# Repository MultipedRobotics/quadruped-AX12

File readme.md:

# AX-12A Quadruped

Features:

- Robotis AX-12A servos
- 4 legs
    - 4 servos per leg for added degrees of freedom
- Raspberry Pi 3 controlled w/camera
- Robotis lidar for obstacle avoidance and SLAM
- 12V power system
- Externally powered so no limit on run time
    - A battery could be designed and integrated

# Hardware

**Still under development**

- [Mechanical Hardware](mechanical/)
- [Electrical Hardware](electrical/)

# Software

Uses [multiped library](https://github.com/MultipedRobotics/multiped/) to control it.

Other SW is TBD until the design is finished

# Software is MIT License

**Copyright (c) 2018 Kevin J. Walchko**

Permission is hereby granted, free of charge, to any person obtaining a
copy of this software and associated documentation files (the
"Software"), to deal in the Software without restriction, including
without limitation the rights to use, copy, modify, merge, publish,
distribute, sublicense, and/or sell copies of the Software, and to
permit persons to whom the Software is furnished to do so, subject to
the following conditions:

The above copyright notice and this permission notice shall be included
in all copies or substantial portions of the Software.

THE SOFTWARE IS PROVIDED "AS IS", WITHOUT WARRANTY OF ANY KIND,
EXPRESS OR IMPLIED, INCLUDING BUT NOT LIMITED TO THE WARRANTIES OF
MERCHANTABILITY, FITNESS FOR A PARTICULAR PURPOSE AND NONINFRINGEMENT.
IN NO EVENT SHALL THE AUTHORS OR COPYRIGHT HOLDERS BE LIABLE FOR ANY
CLAIM, DAMAGES OR OTHER LIABILITY, WHETHER IN AN ACTION OF CONTRACT,
TORT OR OTHERWISE, ARISING FROM, OUT OF OR IN CONNECTION WITH THE
SOFTWARE OR THE USE OR OTHER DEALINGS IN THE SOFTWARE.

---

<p align="center">
    
    <br />The hardware (mechanical/electrical/documentation) is licensed under a <a rel="license" href="http://creativecommons.org/licenses/by-sa/4.0/">Creative Commons Attribution-ShareAlike 4.0 International License</a>.
</p>

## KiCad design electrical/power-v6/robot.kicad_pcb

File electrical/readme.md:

# Electrical

## Raspberry Pi

Adaptor board to connect the RPi to sensors/actuators

## Sensors

[360 Laser Distance Sensor LDS-01 (LIDAR)](http://www.robotis.us/360-laser-distance-sensor-lds-01-lidar/)

## Power

Power distribution board just passes the input power to the 16 AX12 servos and the RPi/Sensors.

### [Pololu 5V Buck Regulator](https://www.pololu.com/product/2851)

### [Pololu 12V Buck Regulator](https://www.pololu.com/product/2885)

# Bill of Materials (BoM)

| Part | Qnty | Each | Cost |
|---|---|---|---|
| Raspberry Pi | 1 | $35 | $35 |
| Lidar | 1 | $180 | $180 |
| RPi AX12 adaptor board | 1 | $20 est. | $20 |
| Power Distrobution board | 1 | $30 est. | $30 |
| Pololu 12V Buck Regulator | 2 | $40 | $80 |
| Pololu 5V Buck Regulator | 1 | $15 | $15 |
| **Total** | | | **$360** |

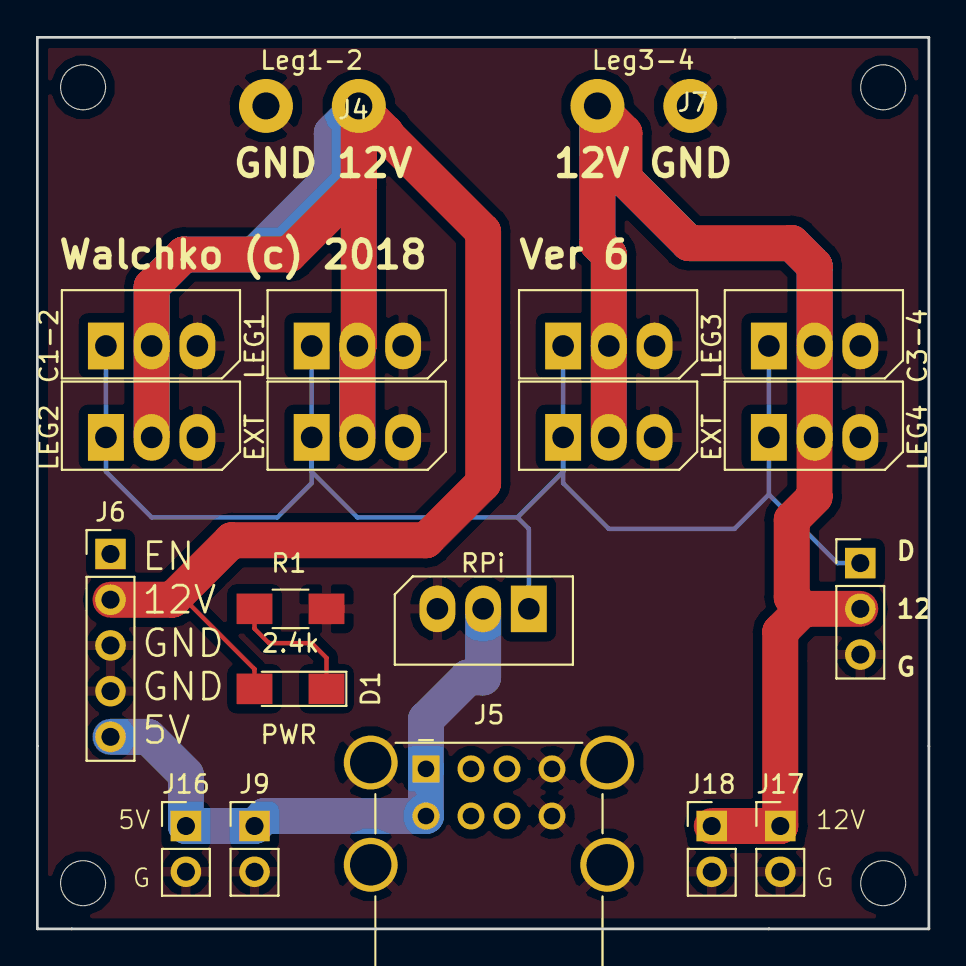
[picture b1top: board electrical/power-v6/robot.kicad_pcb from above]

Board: 2 copper layers, 49.5 x 49.5 mm, 21 parts (1 on the bottom side), 6 nets.

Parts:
D1: PWR; LED_1206_HandSoldering
J1: C1-2; Molex_SPOX-5267_22-03-5035_03x2.54mm_Straight
J2: RPi; Molex_SPOX-5267_22-03-5035_03x2.54mm_Straight
J3: Data; Pin_Header_Straight_1x03_Pitch2.54mm
J4: Leg1-2; WireConnection_1.50mmDrill
J5: USB_A_2_PORT; USB_A_Wuerth_61400826021_Horizontal_Stacked
J6: 5V Pwr; Pin_Header_Straight_1x05_Pitch2.54mm
J7: Leg3-4; WireConnection_1.50mmDrill
J8: LEG1; Molex_SPOX-5267_22-03-5035_03x2.54mm_Straight
J9, J16: 5V; Pin_Header_Straight_1x02_Pitch2.54mm
J10: LEG2; Molex_SPOX-5267_22-03-5035_03x2.54mm_Straight
J11, J13: EXT; Molex_SPOX-5267_22-03-5035_03x2.54mm_Straight
J12: LEG4; Molex_SPOX-5267_22-03-5035_03x2.54mm_Straight
J14: C3-4; Molex_SPOX-5267_22-03-5035_03x2.54mm_Straight
J15: LEG3; Molex_SPOX-5267_22-03-5035_03x2.54mm_Straight
J17, J18: 12V; Pin_Header_Straight_1x02_Pitch2.54mm
LOGO1: Logo_Open_Hardware_Large; OSHW-Logo2_24.3x20mm_SilkScreen
R1: 2.4k; R_1206_HandSoldering

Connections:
+5V: J2.2, J5.1, J5.5, J6.5, J9.1, J16.1
DATA: J1.1, J2.1, J3.1, J8.1, J10.1, J11.1, J12.1, J13.1, J14.1, J15.1
GND: J1.3, J2.3, J3.3, J4.1, J5.4, J5.8, J5.9, J6.3, J6.4, J7.1, J8.3, J9.2, J10.3, J11.3, J12.3, J13.3, J14.3, J15.3, J16.2, J17.2, J18.2, R1.2
unnamed: D1.1, R1.1
unnamed: D1.2, J1.2, J4.2, J6.2, J8.2, J10.2, J11.2
unnamed: J3.2, J7.2, J12.2, J13.2, J14.2, J15.2, J17.1, J18.1

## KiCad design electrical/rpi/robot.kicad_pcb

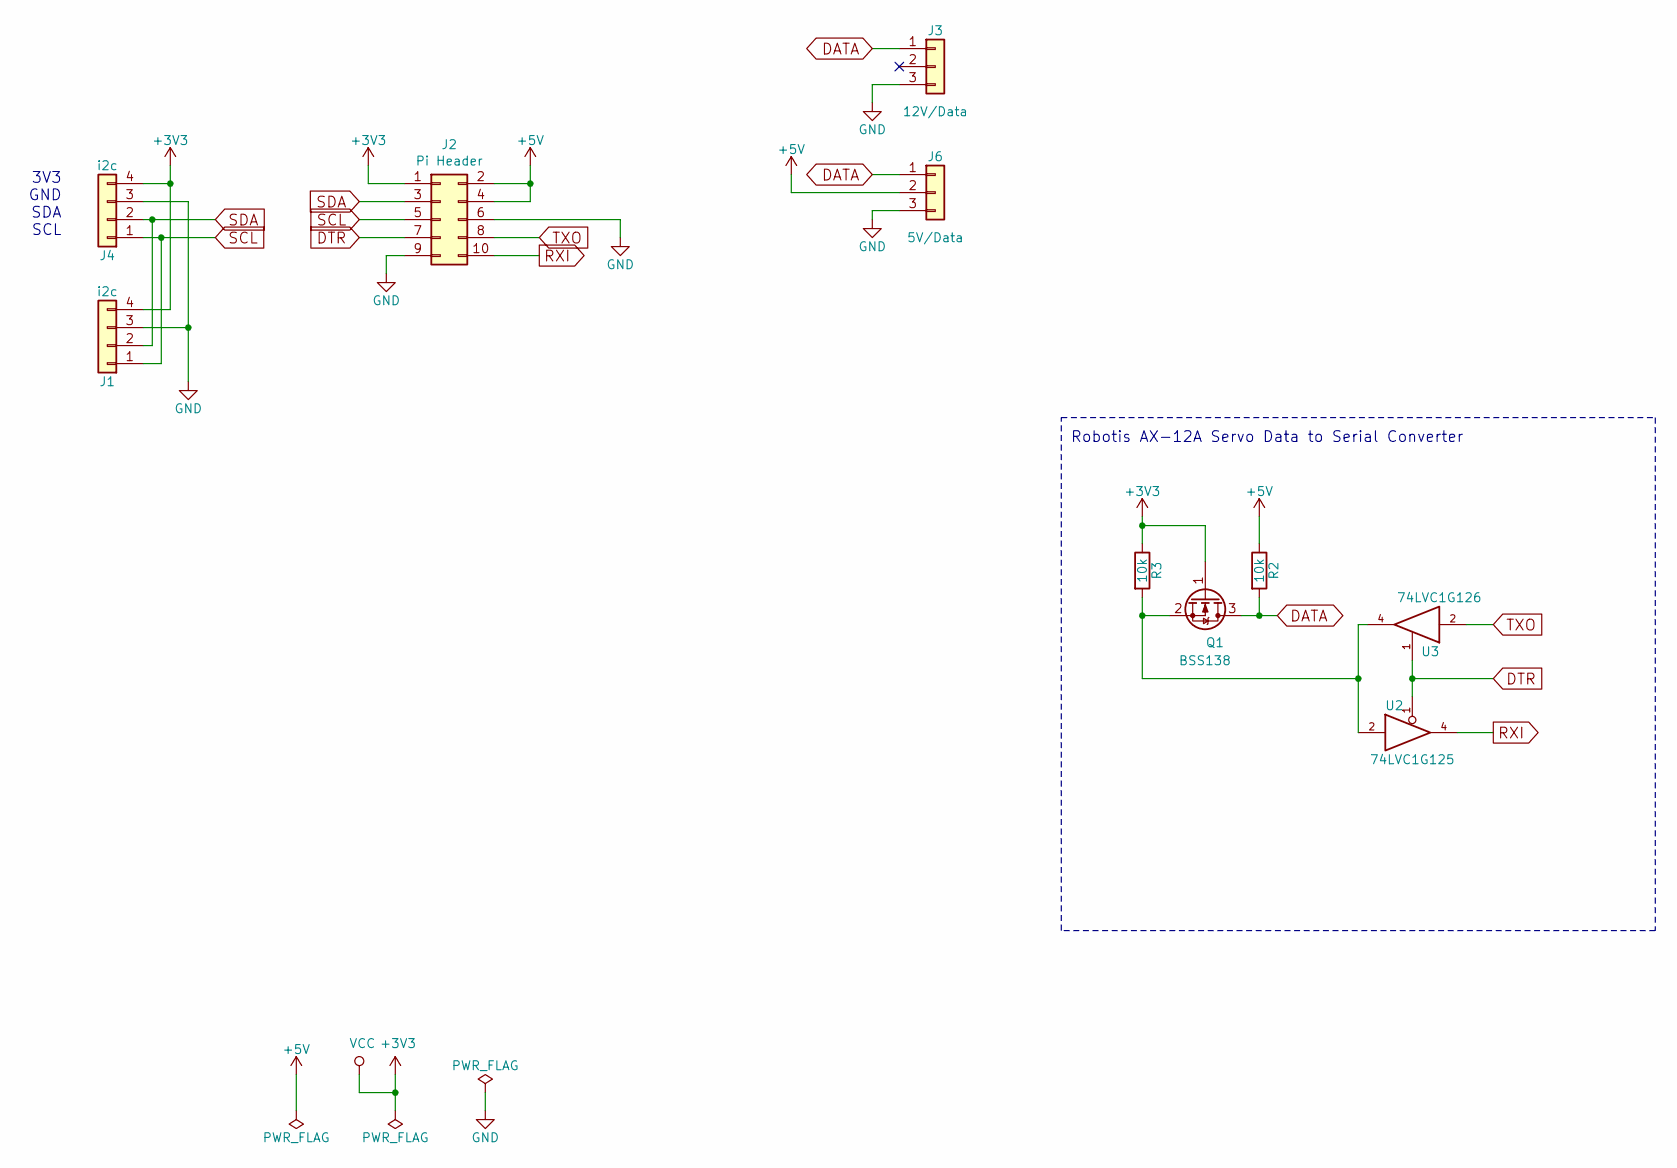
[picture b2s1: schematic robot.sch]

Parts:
J1, J4: i2c; Pin_Header_Straight_1x04_Pitch2.54mm
J2: Pi Header; Pin_Header_Straight_2x05_Pitch2.54mm
J3: 12V/Data; Molex_SPOX-5267_22-03-5035_03x2.54mm_Straight
J6: 5V/Data; Molex_SPOX-5267_22-03-5035_03x2.54mm_Straight
Q1: BSS138; SOT-23
R2, R3: 10k; R_1206_HandSoldering
U2: 74LVC1G125; SOT-23-5_HandSoldering
U3: 74LVC1G126; SOT-23-5_HandSoldering

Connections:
+3V3: J1.4, J2.1, J4.4, Q1.1 (G), R3.1, U2.5 (VCC), U3.5 (VCC)
+5V: J2.2, J2.4, J6.2, R2.1
DATA: J3.1, J6.1, Q1.3 (D), R2.2
DTR: J2.7, U2.1, U3.1
GND: J1.3, J2.6, J2.9, J3.3, J4.3, J6.3, U2.3 (GND), U3.3 (GND)
unnamed: Q1.2 (S), R3.2, U2.2, U3.4
RXI: J2.10, U2.4
SCL: J1.1, J2.5, J4.1
SDA: J1.2, J2.3, J4.2
TXO: J2.8, U3.2

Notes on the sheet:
Robotis AX-12A Servo Data to Serial Converter
3V3 GND SDA SCL

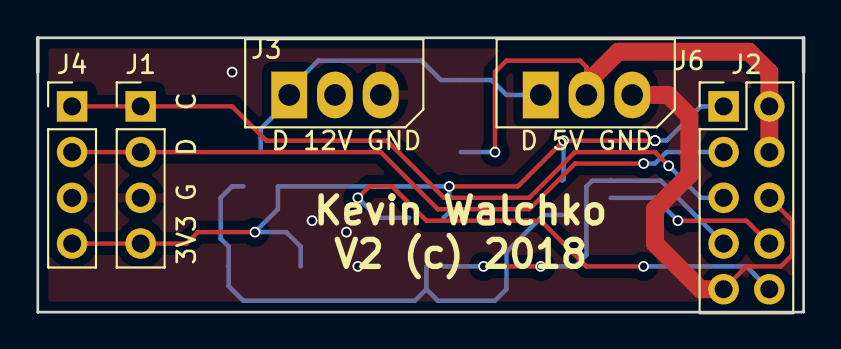
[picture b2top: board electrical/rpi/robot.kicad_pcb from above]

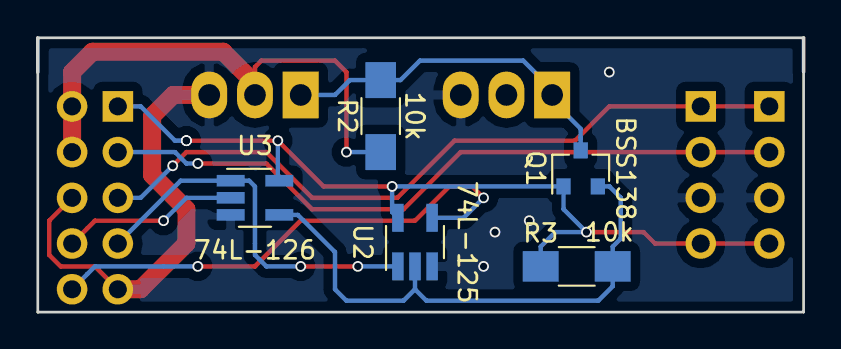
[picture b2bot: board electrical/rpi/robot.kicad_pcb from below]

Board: 2 copper layers, 42.5 x 15.2 mm, 10 parts (5 on the bottom side), 10 nets.

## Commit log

2018-11-27 small fixes
2018-11-27 new board :electric_plug: :bento:
2018-11-28 Update LICENSE
2018-12-01 servos read :lizard: :bento:
2023-05-15 Create deleteme

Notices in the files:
electrical/power-v6/robot.kicad_pcb:
Walchko (c) 2018
electrical/rpi/robot.kicad_pcb:
V2 (c) 2018
readme.md:
CC BY-SA 4.0
